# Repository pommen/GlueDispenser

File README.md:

# Dispener_controller
A custom gluedispenser controller for automated gluing. Based on AtMega 328p

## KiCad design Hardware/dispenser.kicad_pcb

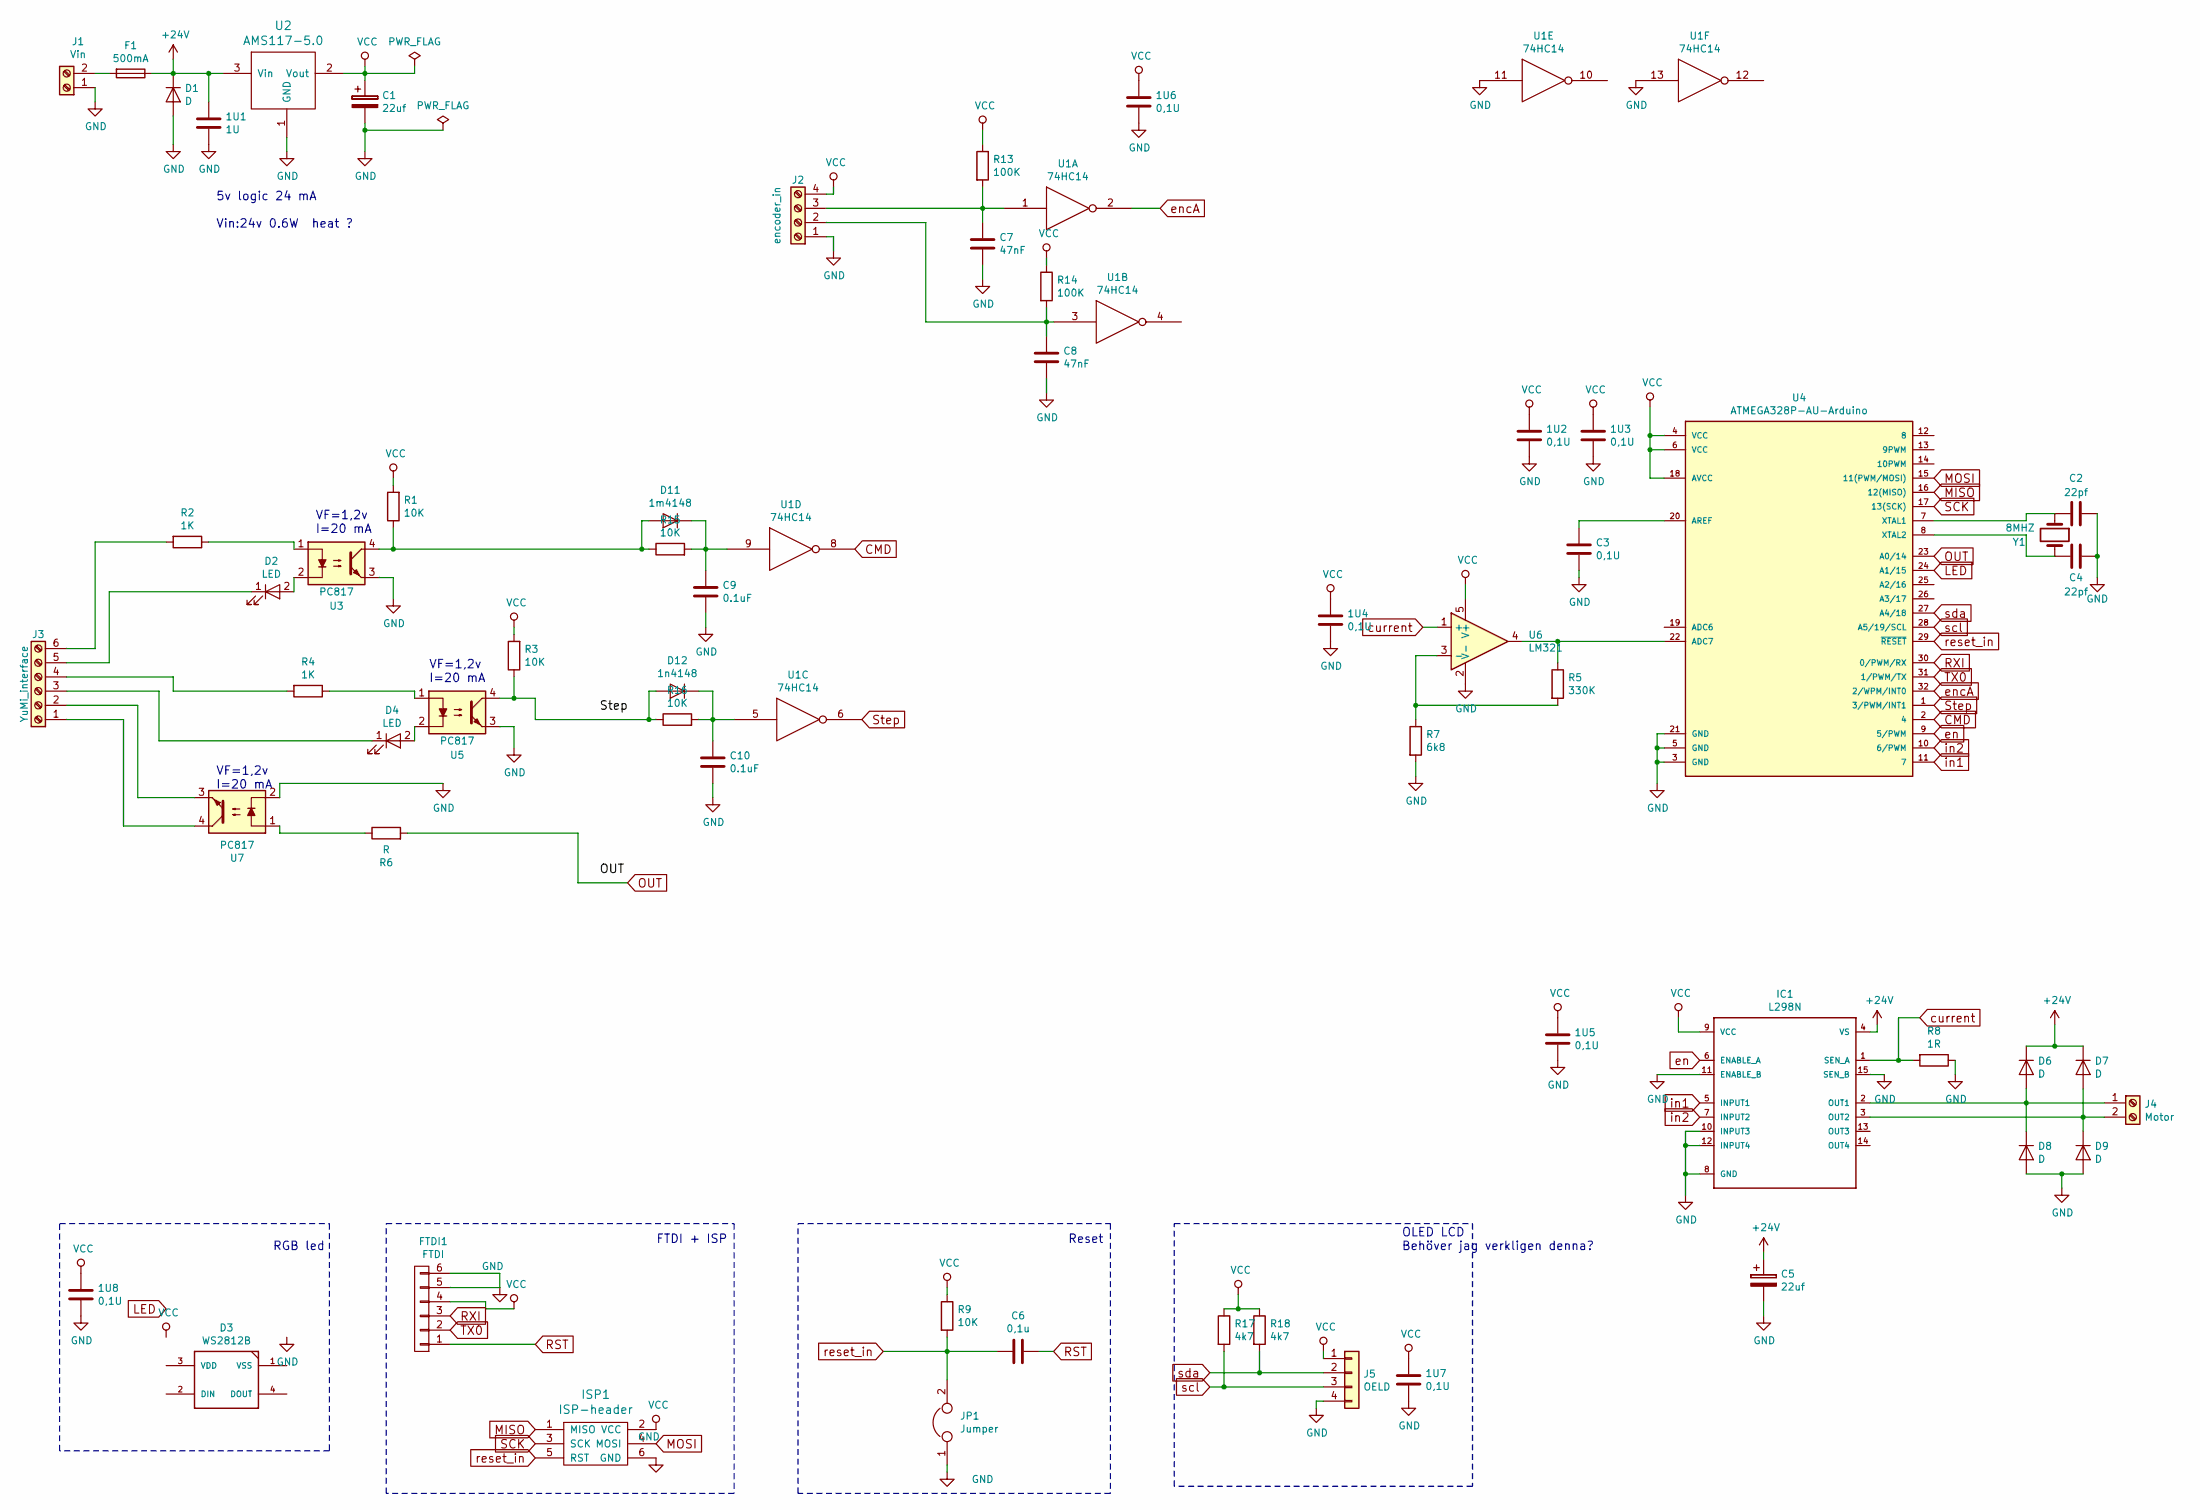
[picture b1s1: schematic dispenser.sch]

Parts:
1U1: 1U; C_0805_HandSoldering
1U2, 1U3, 1U4, 1U5, 1U6, 1U7, 1U8: 0,1U; C_0805_HandSoldering
C1, C5: 22uf; CP_Tantalum_Case-D_EIA-7343-31_Hand
C2, C4: 22pf; C_0805_HandSoldering
C3: 0,1U; C_0805_HandSoldering
C6: 0,1u; C_0805_HandSoldering
C7, C8: 47nF; C_0805_HandSoldering
C9, C10: 0.1uF; C_0805_HandSoldering
D1: D; D_SMB-SMC_Universal_Handsoldering
D2, D4: LED; LED_D3.0mm
D3: WS2812B
D6, D7, D8, D9: D; D_SMA-SMB_Universal_Handsoldering
D11: 1m4148; D_MiniMELF_Handsoldering
D12: 1n4148; D_MiniMELF_Handsoldering
F1: 500mA; Fuse_TE5_Littlefuse-395Series
FTDI1: FTDI; Pin_Header_Straight_1x06_Pitch2.54mm
IC1: L298N; Multiwatt15_V
ISP1: ISP-header; Pin_Header_Straight_2x03_Pitch2.54mm
J1: Vin; TerminalBlock_bornier-2_P5.08mm
J2: encoder_in; Socket_Strip_Straight_1x04_Pitch2.54mm
J3: YuMi_interface; Socket_Strip_Straight_1x06_Pitch2.54mm
J4: Motor; TerminalBlock_bornier-2_P5.08mm
J5: OELD; Pin_Header_Straight_1x04_Pitch2.54mm
JP1: Jumper; SOLDER-JUMPER_1-WAY
R1, R3, R9, R15, R16: 10K; R_0805_HandSoldering
R2, R4: 1K; R_0805_HandSoldering
R5: 330K; R_0805_HandSoldering
R6: R; R_0805_HandSoldering
R7: 6k8; R_0805_HandSoldering
R8: 1R; R_Axial_DIN0516_L15.5mm_D5.0mm_P20.32mm_Horizontal
R13, R14: 100K; R_0805_HandSoldering
R17, R18: 4k7; R_0805_HandSoldering
U1: 74HC14; DIP-14_W7.62mm_LongPads
U2: AMS117-5.0; SOT-223
U3, U5, U7: PC817; 817opto
U4: ATMEGA328P-AU-Arduino; TQFP-32_7x7mm_Pitch0.8mm
U6: LM321; SOT-23-5
Y1: 8MHZ; Crystal_HC18-U_Vertical

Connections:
+24V: 1U1.1, C5.1, D1.1 (K), D6.1 (K), D7.1 (K), F1.1, IC1.4 (VS), U2.3 (Vin)
CMD: U1.8, U4.2 (4)
GND: 1U1.2, 1U2.2, 1U3.2, 1U4.2, 1U5.2, 1U6.2, 1U7.2, 1U8.2, C1.2, C2.1, C3.2, C4.1, C5.2, C7.2, C8.2, C9.2, C10.2, D1.2 (A), D8.2 (A), D9.2 (A), FTDI1.5, FTDI1.6, IC1.8 (GND), IC1.10 (INPUT3), IC1.11 (ENABLE_B), IC1.12 (INPUT4), IC1.15 (SEN_B), ISP1.6 (GND), J1.1, J2.1, J5.4, JP1.1, R7.2, R8.1, U1.7 (GND), U1.11, U1.13, U2.1 (GND), U3.3, U4.3 (GND), U4.5 (GND), U4.21 (GND), U5.3, U6.2 (V-), U7.2
LED: U4.24 (A1/15)
MISO: ISP1.1 (MISO), U4.16 (12(MISO))
MOSI: ISP1.4 (MOSI), U4.15 (11(PWM/MOSI))
unnamed: C2.2, U4.7 (XTAL1), Y1.1
unnamed: C3.1, U4.20 (AREF)
unnamed: C4.2, U4.8 (XTAL2), Y1.2
unnamed: C7.1, J2.3, R13.2, U1.1
unnamed: C8.1, J2.2, R14.2, U1.3
unnamed: C9.1, D11.1 (K), R15.2, U1.9
unnamed: C10.1, D12.1 (K), R16.2, U1.5
unnamed: D2.1 (K), J3.5
unnamed: D2.2 (A), U3.2
unnamed: D4.1 (K), J3.3
unnamed: D4.2 (A), U5.2
unnamed: D6.2 (A), D8.1 (K), IC1.2 (OUT1), J4.1
unnamed: D7.2 (A), D9.1 (K), IC1.3 (OUT2), J4.2
unnamed: D11.2 (A), R1.1, R15.1, U3.4
unnamed: D12.2 (A), R3.1, R16.1, U5.4
unnamed: F1.2, J1.2
unnamed: J3.1, U7.4
unnamed: J3.2, U7.3
unnamed: J3.4, R4.2
unnamed: J3.6, R2.2
unnamed: R2.1, U3.1
unnamed: R4.1, U5.1
unnamed: R5.1, U4.22 (ADC7), U6.4
unnamed: R5.2, R7.1, U6.3 (-)
unnamed: R6.1, U7.1
OUT: R6.2, U4.23 (A0/14)
RST: C6.1, FTDI1.1
RXI: FTDI1.3, U4.30 (0/PWM/RX)
SCK: ISP1.3 (SCK), U4.17 (13(SCK))
Step: U1.6, U4.1 (3/PWM/INT1)
TX0: FTDI1.2, U4.31 (1/PWM/TX)
VCC: 1U2.1, 1U3.1, 1U4.1, 1U5.1, 1U6.1, 1U7.1, 1U8.1, C1.1, FTDI1.4, IC1.9 (VCC), ISP1.2 (VCC), J2.4, J5.1, R1.2, R3.2, R9.1, R13.1, R14.1, R17.1, R18.1, U1.14 (VCC), U2.2 (Vout), U4.4 (VCC), U4.6 (VCC), U4.18 (AVCC), U6.5 (V+)
current: IC1.1 (SEN_A), R8.2, U6.1 (+)
en: IC1.6 (ENABLE_A), U4.9 (5/PWM)
encA: U1.2, U4.32 (2/WPM/INT0)
in1: IC1.5 (INPUT1), U4.11 (7)
in2: IC1.7 (INPUT2), U4.10 (6/PWM)
reset_in: C6.2, ISP1.5 (RST), JP1.2, R9.2, U4.29 (~RESET~)
scl: J5.3, R17.2, U4.28 (A5/19/SCL)
sda: J5.2, R18.2, U4.27 (A4/18)

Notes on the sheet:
FTDI + ISP
5v logic 24 mA Vin:24v 0.6W heat ?
OLED LCD Behöver jag verkligen denna?
Reset
RGB led
VF=1,2v I=20 mA

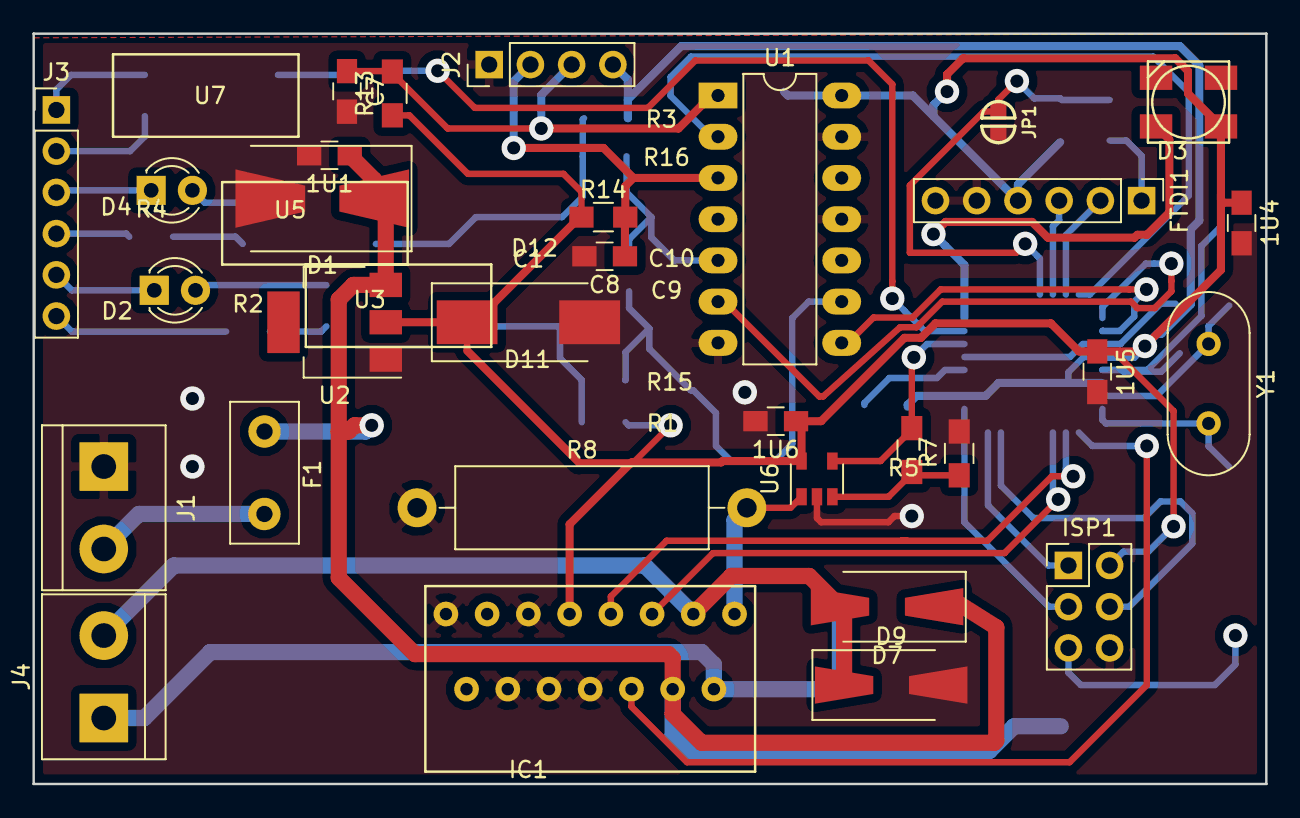
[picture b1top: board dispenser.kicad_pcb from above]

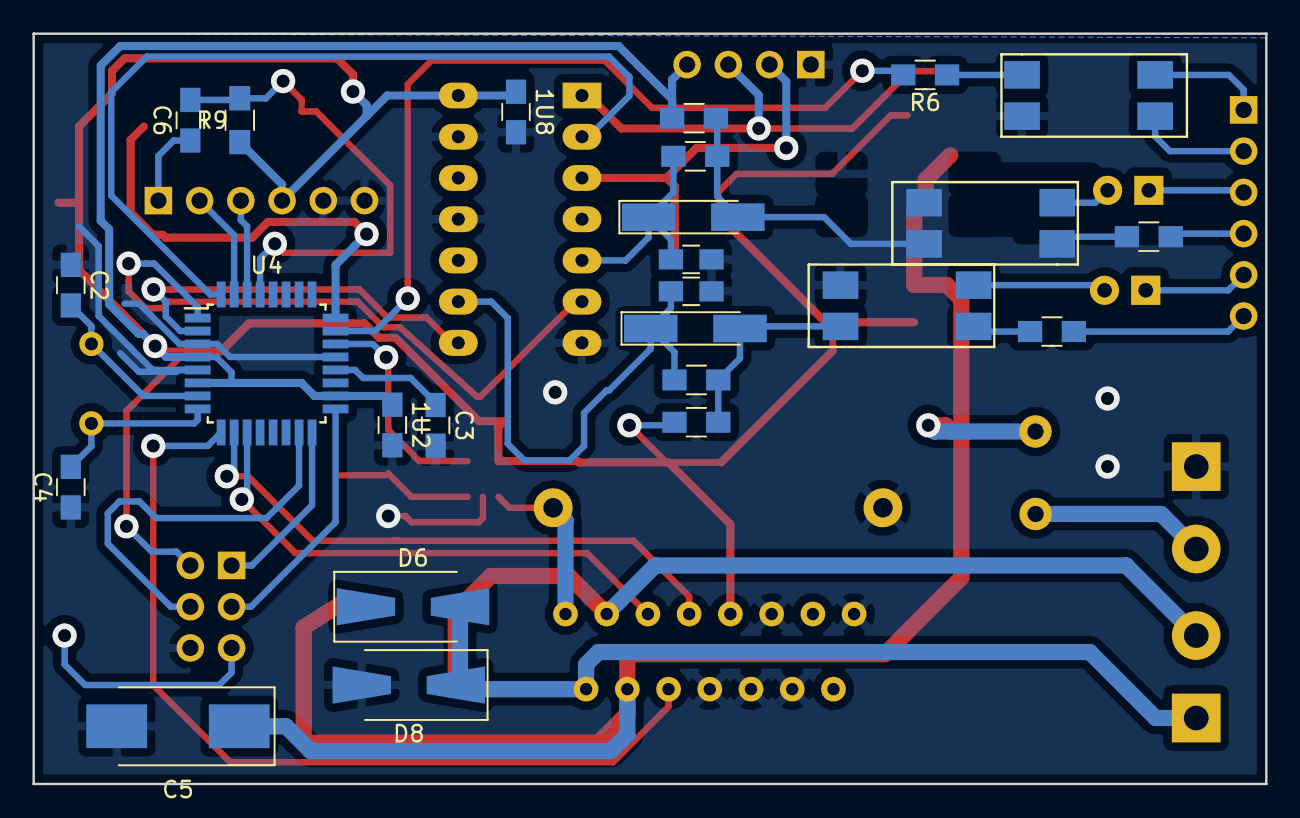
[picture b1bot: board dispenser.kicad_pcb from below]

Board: 2 copper layers, 75.9 x 46.2 mm, 56 parts (25 on the bottom side), 43 nets.

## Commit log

2017-11-30 added limitswitches
2018-01-02 Added back algorithm
2018-01-25 New version with two dispernsers on one board. Changed from atmega328p to stm23f103c8
2018-01-28 sync old atmega files
